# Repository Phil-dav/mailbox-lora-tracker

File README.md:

# Mailbox LoRa Tracker

A weight-sensing mailbox notifier built around a Heltec WiFi LoRa 32 (V2) and
an HX711 + 4 load cells. A door-triggered latching relay wakes the board with
zero standby current, it weighs whatever was just dropped in, sends the
result over LoRa to a receiver elsewhere in the house, waits for an ACK, then
cuts its own power.

Built for a shared/collective mailbox (multiple households behind one
postal-carrier door), where a simple door contact alone can't tell "someone
delivered to me" from "a neighbor's delivery, same door."

## How it works

```
Door opens (mechanical contact, no power needed)
  -> latching relay powers the board
  -> tare the HX711 (empty platform reference)
  -> wait for the door to close, or a safety timeout
  -> weigh again, with a settling/stability loop
     (absorbs shocks from a dropped/thrown package)
  -> if weight > threshold: send "COLIS:<grams>" over LoRa,
     wait for an ACK (bounded retries)
  -> cut its own power (transistor + relay), whatever happened above
```

Every branch converges on the same final power-cutoff step, so the board
always ends up switching itself off in bounded time, regardless of whether
a package was actually detected or an ACK came back.

## Hardware

- Heltec WiFi LoRa 32 V2 (ESP32 + SX127x), one per side (sender/receiver)
- HX711 + 4x 50kg half-bridge load cell sensors (bathroom-scale style)
- 2-relay latching power circuit (door contact triggers wake, transistor
  cuts power at end of cycle)
- 2nd door contact (independent GPIO) to detect when the door closes

### GPIO map (sender)

| GPIO | Function |
|---|---|
| 33 | Power cutoff (drives the relay-latch transistor) |
| 13 | 2nd door contact (detects door close) |
| 17 | HX711 DT |
| 23 | HX711 SCK |
| 5 / 27 / 19 / 18 | LoRa SPI (SCK / MOSI / MISO / NSS) — fixed on-module wiring |
| 14 | LoRa reset — fixed on-module wiring |
| 4 / 15 | OLED I2C (SDA / SCL) — fixed on-module wiring |
| 21 / 16 | OLED Vext / reset — fixed on-module wiring |

GPIO 34/35 are hardwired on the Heltec module to the SX127x's DIO2/DIO1 and
must never be reused for anything external.

## Repo contents

- `src/bin/courrier_emetteur.rs` — sender firmware (in the mailbox)
- `src/bin/courrier_recepteur.rs` — receiver firmware (indoors, mains-powered)
- `src/sx127x.rs` — minimal SX127x LoRa driver (SPI, ping/ack style)
- `KiCAD/Latch colis/` — schematic + PCB for the power-latch/relay board,
  plus etching files (single-sided, hand-etched)

> The schematic uses a couple of custom symbols/footprints (HX711 module,
> Heltec pinout) from a personal KiCad library that isn't included here yet
> — expect missing-footprint warnings if you open the project directly.

## Status

Weighing is calibrated and validated on the bench (13g to 2.25kg, <1% error
against a reference scale). Mechanical assembly (load cell mounting, door
contacts on the shared mailbox door) is still in progress.

## License

MIT — see [LICENSE](LICENSE).

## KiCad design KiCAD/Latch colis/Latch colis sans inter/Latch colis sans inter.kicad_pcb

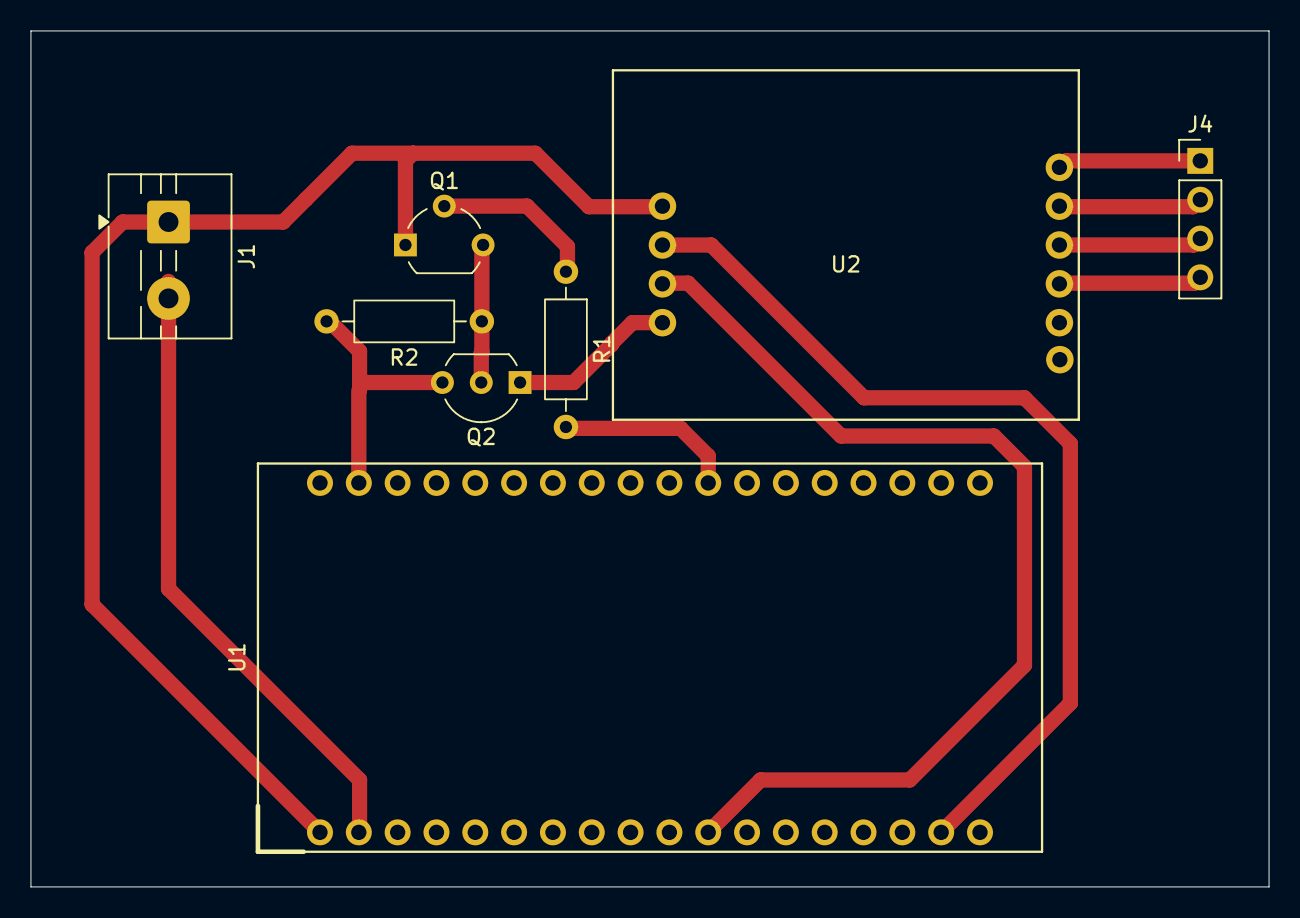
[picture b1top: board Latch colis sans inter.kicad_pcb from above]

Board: 2 copper layers, 81.0 x 56.0 mm, 8 parts (0 on the bottom side), 13 nets.

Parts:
J1: KF301-2P
J4: Jauges; PinHeader_1x04_P2.54mm_Vertical
Q1: 2N2222A; TO-92_Wide
Q2: BS250; TO-92_Inline_Wide
R1, R2: 1k; R_Axial_DIN0207_L6.3mm_D2.5mm_P10.16mm_Horizontal
U1: Heltec_LoRa32_V2_RST_side; MODULE_ESP32_LORA_V2.0
U2: Module HX711; HX711_Module

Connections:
/+3.3V HX711: Q2.3 (S), R2.2, U1.20 (3V3)
/+5V: J1.2, U1.2 (5V)
/DT: U1.17, U2.8 (DT)
/SCK: U1.11 (23), U2.9 (SCK)
GND: J1.1, Q1.1, U1.1 (GND), U2.7 (GND)
unnamed: J4.1, U2.1 (E+)
unnamed: J4.2, U2.2 (E-)
unnamed: J4.3, U2.3 (A+)
unnamed: J4.4, U2.4 (A-)
unnamed: Q1.2, R1.1
unnamed: Q2.1 (D), U2.10 (VCC)
unnamed: Q1.3, Q2.2 (G), R2.1
unnamed: R1.2, U1.29 (33)

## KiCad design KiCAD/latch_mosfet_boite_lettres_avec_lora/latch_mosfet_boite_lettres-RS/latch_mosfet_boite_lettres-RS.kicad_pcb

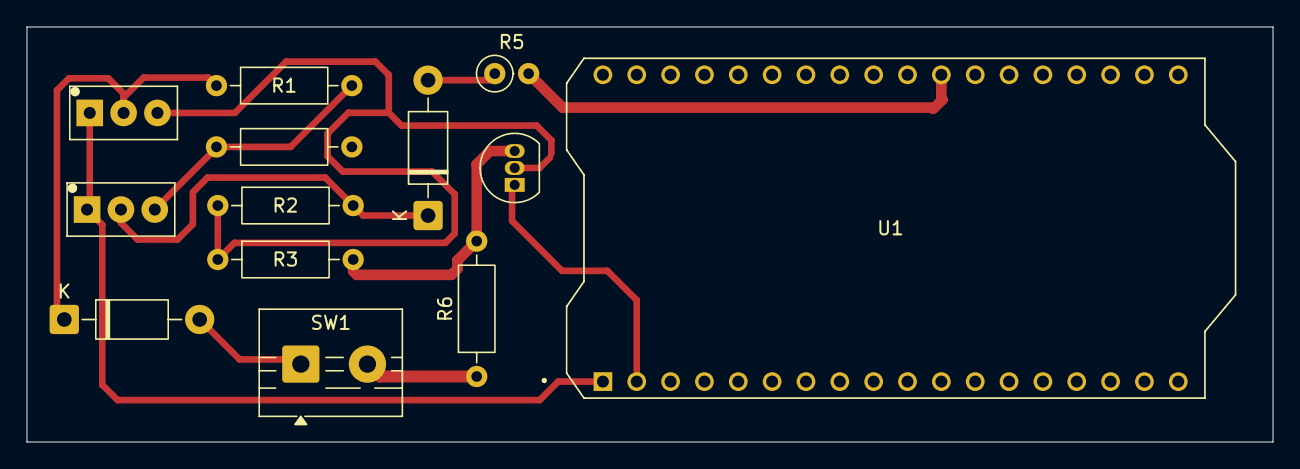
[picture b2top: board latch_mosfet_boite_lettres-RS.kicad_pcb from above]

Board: 2 copper layers, 93.5 x 31.1 mm, 13 parts (0 on the bottom side), 11 nets.

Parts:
D1, D2: 1N4002; D_DO-41_SOD81_P10.16mm_Horizontal
Q1, Q2: 2N2222A; TO-92_Inline_Wide_5.08mm
Q4: ZVP2106A; TO-92_Inline
R1, R2, R3, R4, R6: R; R_Axial_DIN0207_L6.3mm_D2.5mm_P10.16mm_Horizontal
R5: R; R_Axial_DIN0207_L6.3mm_D2.5mm_P2.54mm_Vertical
SW1: SW_Push; TerminalBlock_MaiXu_MX126-5.0-02P_1x02_P5.00mm
U1: Heltec_LoRa32_V2_RST_side; MODULE_ESP32_LORA_V2.0

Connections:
+5V: Q4.3 (S), R3.2, R4.2, R6.2
GND: Q1.1, Q2.1, U1.1 (GND)
unnamed: D1.2 (A), SW1.1
unnamed: D1.1 (K), Q1.2, R1.1
unnamed: D2.2 (A), R5.1
unnamed: D2.1 (K), Q2.2, R2.2
unnamed: Q2.3, R1.2, R4.1
unnamed: Q4.1 (D), U1.2 (5V)
unnamed: Q1.3, Q4.2 (G), R2.1, R3.1
unnamed: R6.1, SW1.2
unnamed: R5.2, U1.29 (33)

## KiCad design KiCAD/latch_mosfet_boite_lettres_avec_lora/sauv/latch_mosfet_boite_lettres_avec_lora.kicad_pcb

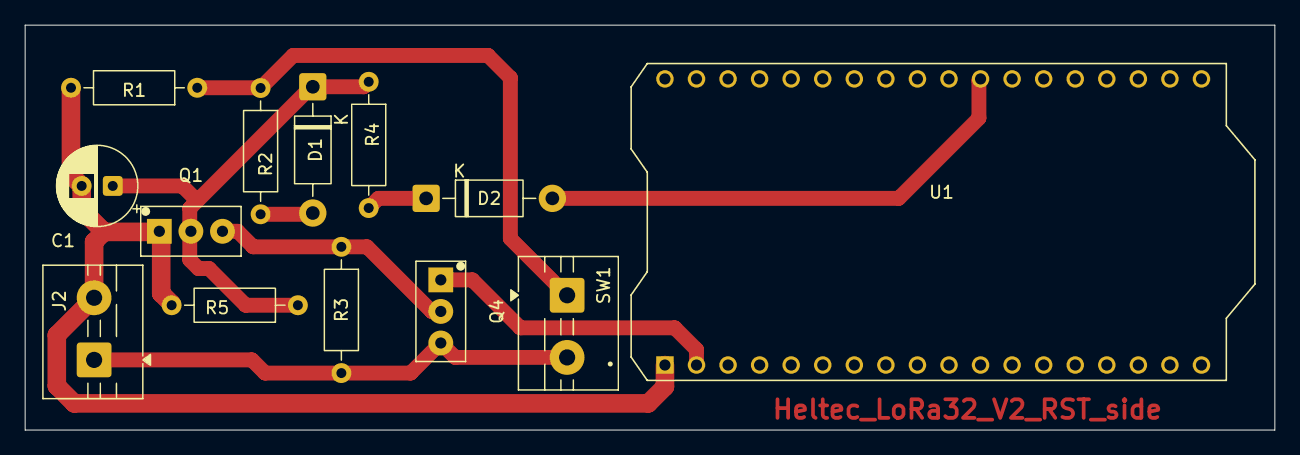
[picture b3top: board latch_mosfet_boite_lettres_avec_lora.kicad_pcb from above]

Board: 2 copper layers, 100.6 x 32.6 mm, 13 parts (0 on the bottom side), 9 nets.

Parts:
C1: 220µF; CP_Radial_D6.3mm_P2.50mm
D1, D2: 1N4002; D_DO-41_SOD81_P10.16mm_Horizontal
J2: Alim; TerminalBlock_MaiXu_MX126-5.0-02P_1x02_P5.00mm
Q1: 2N2222A; TO-92_Inline_Wide_5.08mm
Q4: ZVP2106A; TO-92_Inline_Wide_5.08mm
R1, R3: 220k; R_Axial_DIN0207_L6.3mm_D2.5mm_P10.16mm_Horizontal
R2: 1.5k; R_Axial_DIN0207_L6.3mm_D2.5mm_P10.16mm_Horizontal
R4: 820; R_Axial_DIN0207_L6.3mm_D2.5mm_P10.16mm_Horizontal
R5: 100k; R_Axial_DIN0207_L6.3mm_D2.5mm_P10.16mm_Horizontal
SW1: SW_Push; TerminalBlock_MaiXu_MX126-5.0-02P_1x02_P5.00mm
U1: U1; MODULE_ESP32_LORA_V2.0

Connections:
+5V: J2.1, Q4.3 (S), R3.2, SW1.2
/PWR_OFF (GPIO 33): D2.2 (A), U1.29 (33)
/Vin (Lora): Q4.1 (D), U1.2 (5V)
GND: C1.2, J2.2, Q1.1, R1.2, R5.2, U1.1 (GND)
unnamed: D1.2 (A), R2.2
unnamed: C1.1, D1.1 (K), Q1.2, R4.1, R5.1
unnamed: D2.1 (K), R4.2
unnamed: Q1.3, Q4.2 (G), R3.1
unnamed: R1.1, R2.1, SW1.1
